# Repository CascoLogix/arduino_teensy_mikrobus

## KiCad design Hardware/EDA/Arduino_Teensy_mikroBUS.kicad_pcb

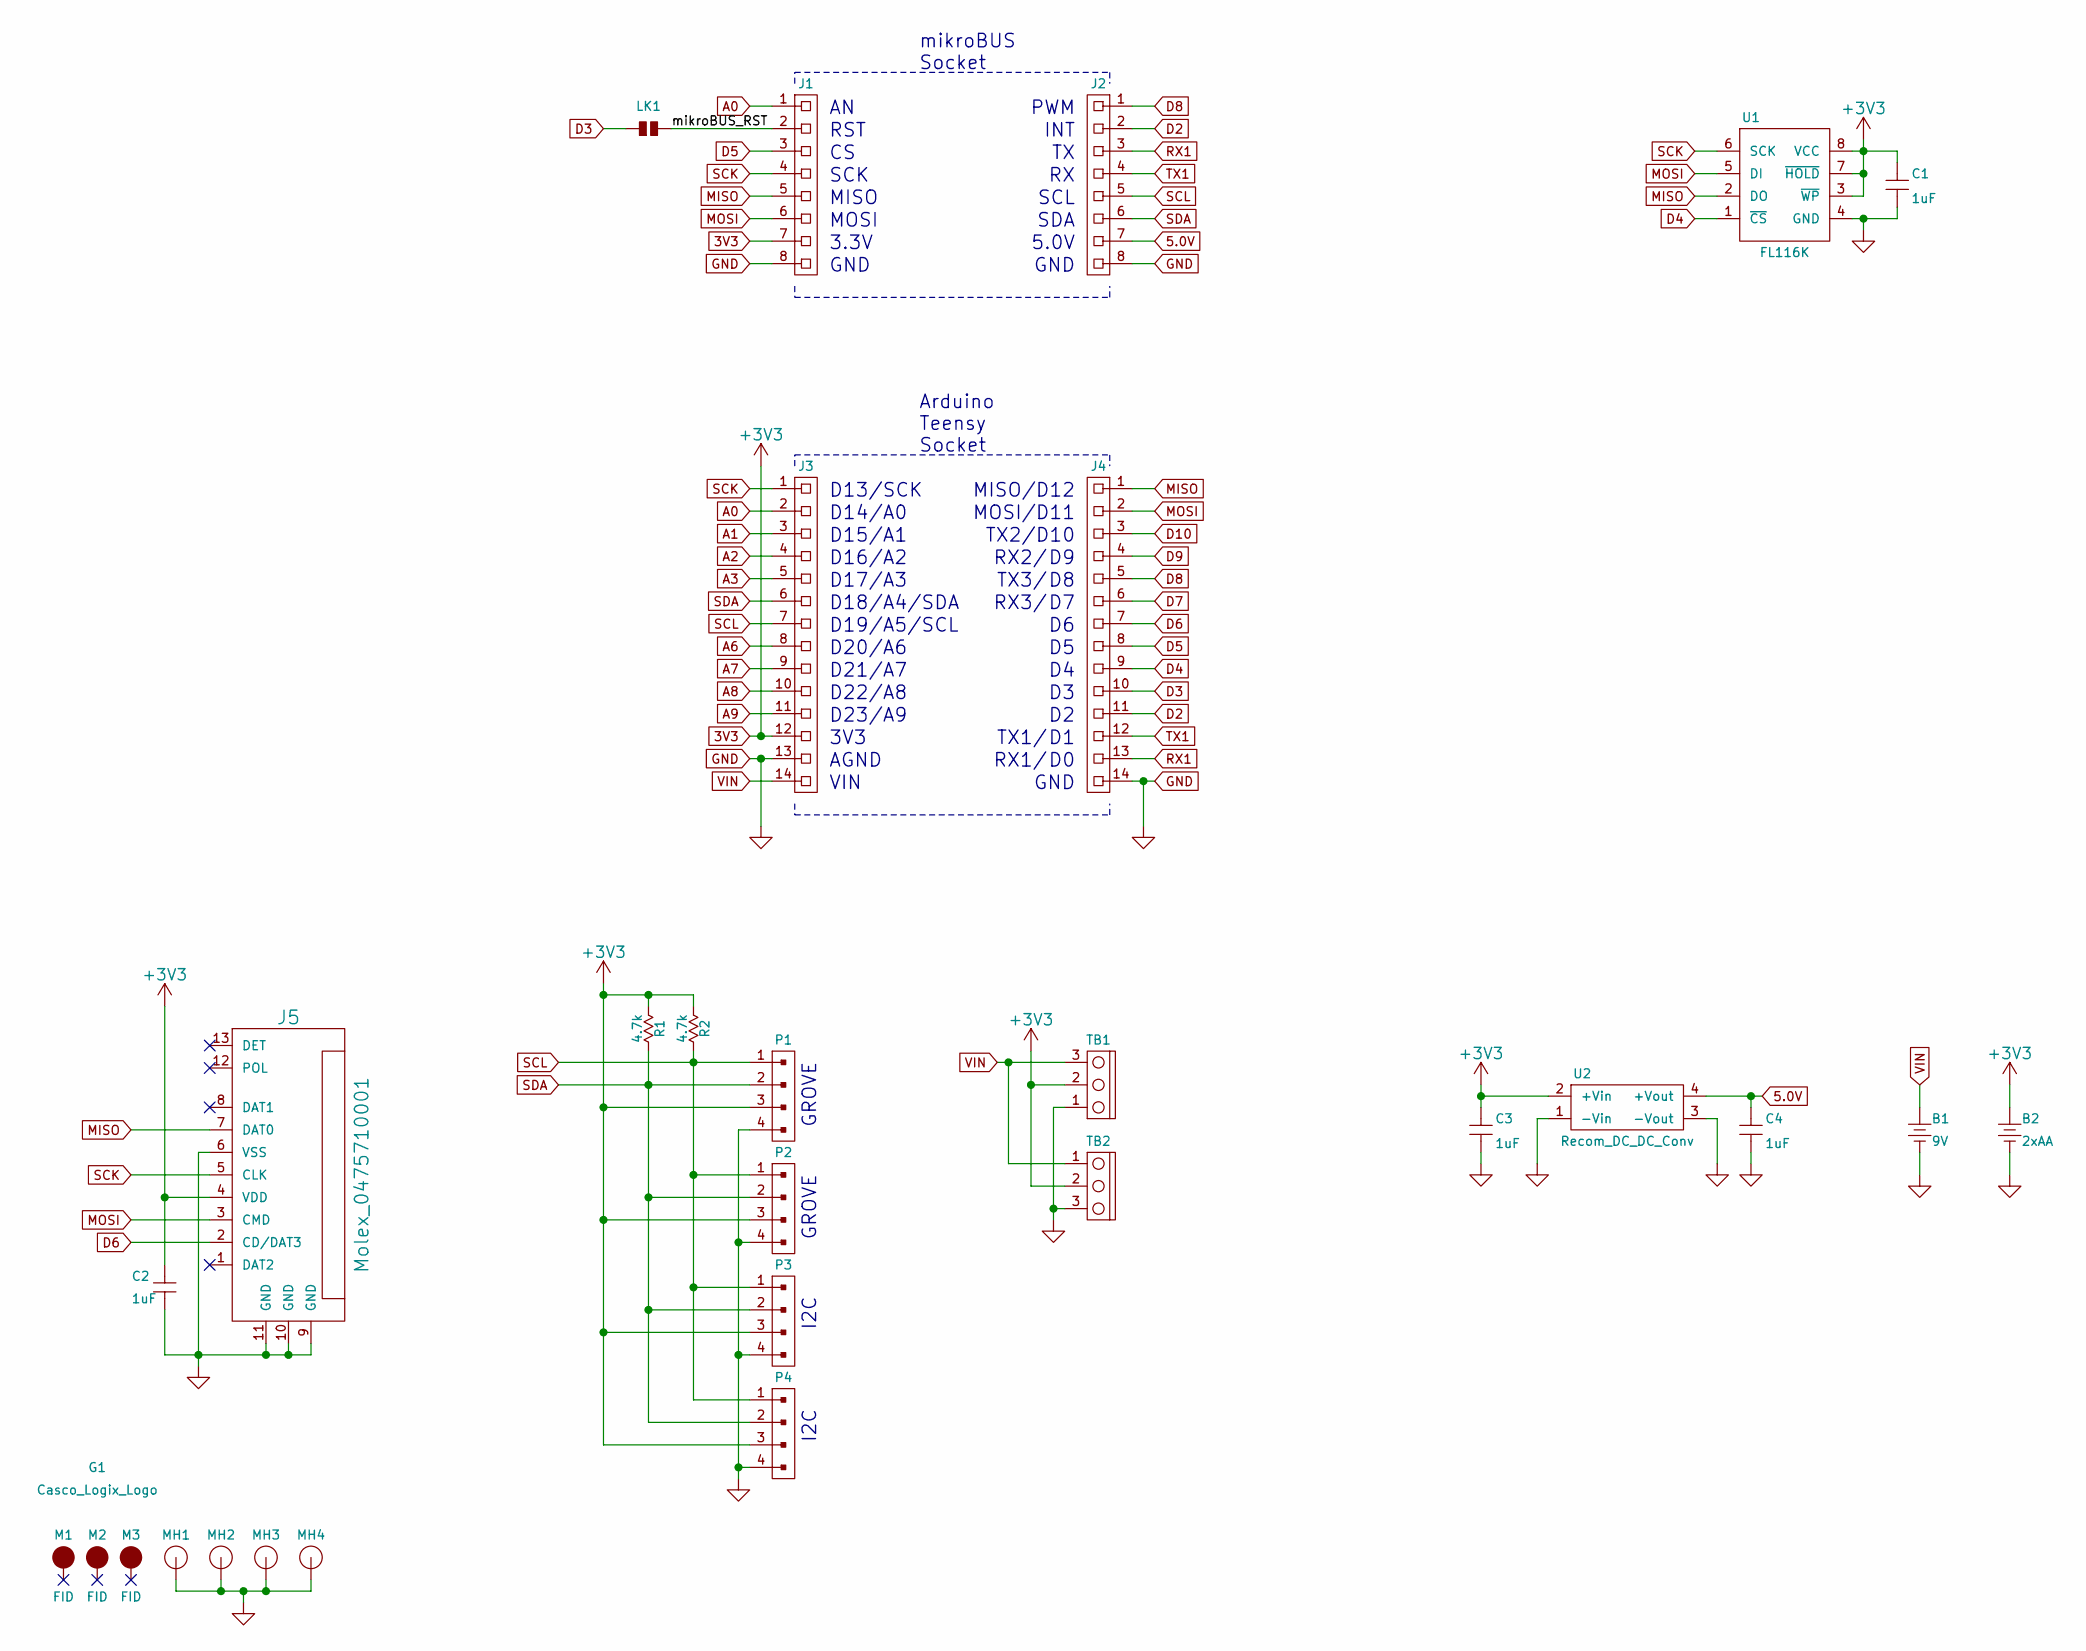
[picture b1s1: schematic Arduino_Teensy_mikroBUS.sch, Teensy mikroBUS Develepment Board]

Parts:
B1: 9V; BC9VPC
B2: 2xAA; Keystone_2462_2AA
C1, C2, C3, C4: 1uF; 0603
G1: Casco_Logix_Logo; Casco_Logix_Logo_7x7MM
J1, J2: HEADER_F_2.54MM_1R8P_ST_AU_PTH
J3, J4: HEADER_F_2.54MM_1R14P_ST_AU_PTH
J5: Molex_0475710001
LK1: SOLDER_LINK_NO
M1, M2, M3: FID; FIDUCIAL
MH1, MH2, MH3, MH4: MTG_HOLE; MH_#6
P1, P2, P3, P4: HEADER_M_2.54MM_1R4P_ST_AU_PTH
R1, R2: 4.7k; R0603
TB1, TB2: OSTVN_1x3; TB_100MIL_1R3P_PTH
U1: FL116K; SO-8
U2: Recom_DC_DC_Conv; Recom_ROE-3.305S

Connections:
3V3: B2.1 (+), C1.1, C2.1, C3.1, J1.7, J3.12, J5.4 (VDD), P1.3, P2.3, P3.3, P4.3, R1.1, R2.1, TB1.2, TB2.2, U1.3 (~WP), U1.7 (~HOLD), U1.8 (VCC), U2.2 (+Vin)
5.0V: C4.1, J2.7, U2.4 (+Vout)
A0: J1.1, J3.2
A1: J3.3
A2: J3.4
A3: J3.5
A6: J3.8
A7: J3.9
A8: J3.10
A9: J3.11
D2: J2.2, J4.11
D3: J4.10, LK1.1
D4: J4.9, U1.1 (~CS)
D5: J1.3, J4.8
D6: J4.7, J5.2 (CD/DAT3)
D7: J4.6
D8: J2.1, J4.5
D9: J4.4
D10: J4.3
GND: B1.2 (-), B2.2 (-), C1.2, C2.2, C3.2, C4.2, J1.8, J2.8, J3.13, J4.14, J5.6 (VSS), J5.9 (GND), J5.10 (GND), J5.11 (GND), MH1.~, MH2.~, MH3.~, MH4.~, P1.4, P2.4, P3.4, P4.4, TB1.1, TB2.3, U1.4 (GND), U2.1 (-Vin), U2.3 (-Vout)
MISO: J1.5, J4.1, J5.7 (DAT0), U1.2 (DO)
MOSI: J1.6, J4.2, J5.3 (CMD), U1.5 (DI)
RX1: J2.3, J4.13
SCK: J1.4, J3.1, J5.5 (CLK), U1.6 (SCK)
SCL: J2.5, J3.7, P1.1, P2.1, P3.1, P4.1, R2.2
SDA: J2.6, J3.6, P1.2, P2.2, P3.2, P4.2, R1.2
TX1: J2.4, J4.12
VIN: B1.1 (+), J3.14, TB1.3, TB2.1
mikroBUS_RST: J1.2, LK1.2

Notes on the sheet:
mikroBUS Socket
Arduino Teensy Socket
RST
SCK
MISO
MOSI
3.3V
GND
PWM
INT
SCL
SDA
5.0V
D10
/A0
3V3
AGND
VIN
/A4/SDA
/A3
GROVE
I2C
MOSI/D11
MISO/D12
D13/SCK
D16
D17
D23
D22
D21
D20
D19
D18
D15
D14
/A2
/A1
/A5/SCL
/A9
/A8

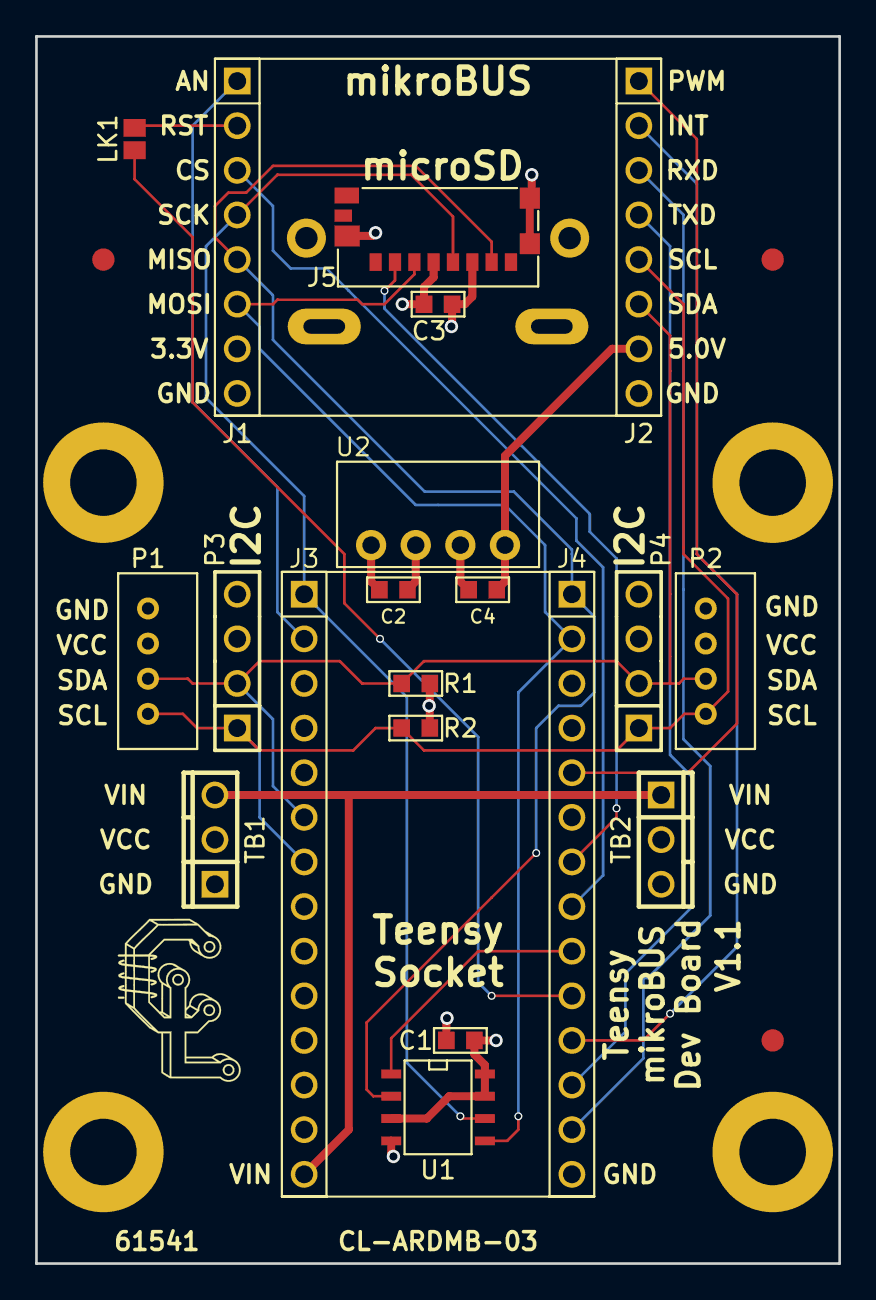
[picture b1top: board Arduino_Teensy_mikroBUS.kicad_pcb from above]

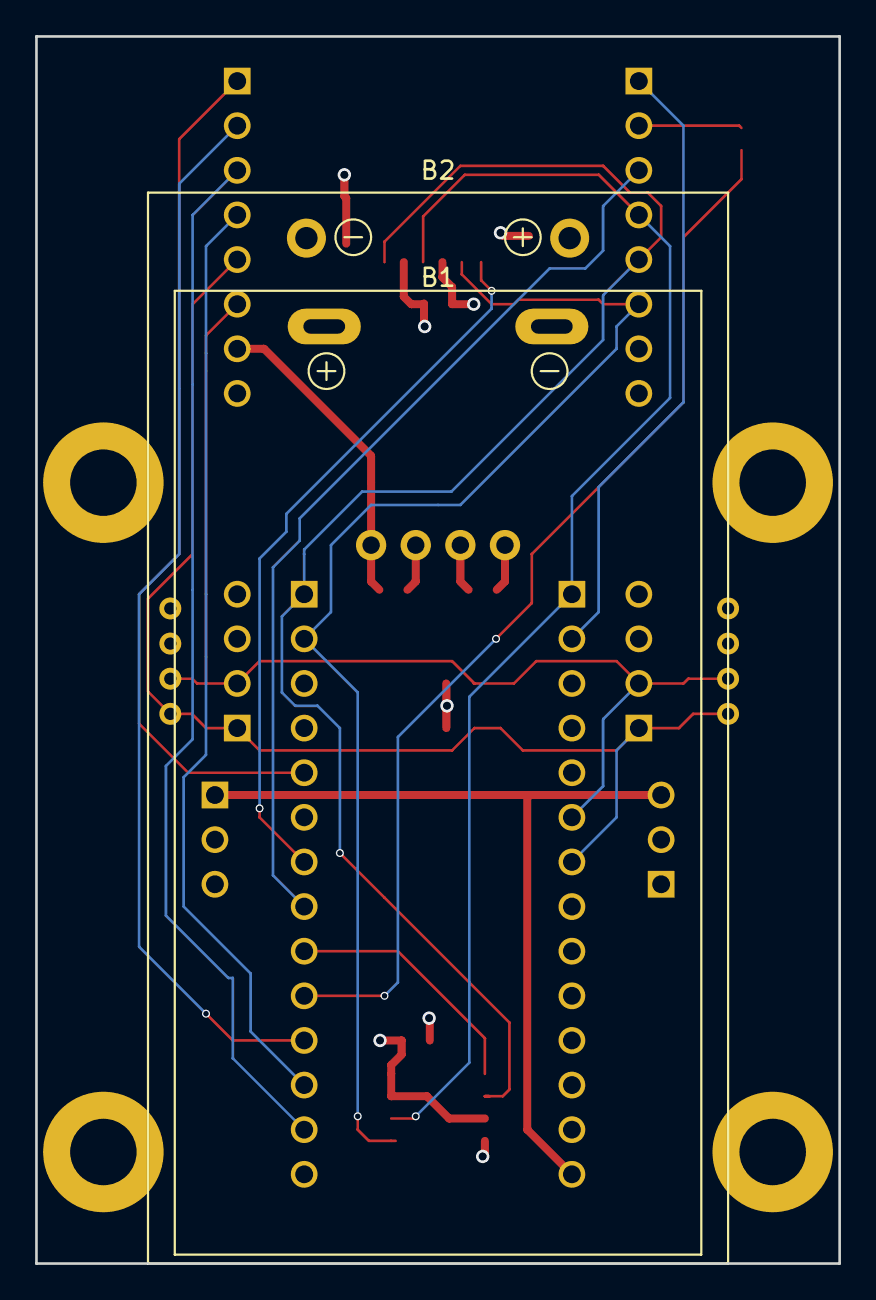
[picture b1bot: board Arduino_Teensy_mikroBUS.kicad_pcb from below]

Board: 4 copper layers, 45.7 x 69.8 mm, 30 parts (2 on the bottom side), 19 nets.

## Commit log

2017-12-28 Initial commit.
2017-12-29 Updated schematic, netlist and read in netlist to PCB file. Added pinouts for Teensy.
2017-12-29 Completed PCB layout, added PCB render image, generated gerbers and schematic.
2018-01-06 Changed PCB outline/size to accomodate mounting holes, but still fit in enclosure. Regenerated Gerbers and PCB render images.
2018-01-14 Adjustment of mounting hole locations was missed. Corrected and updated gerbers and dimensions.
2018-02-17 Added comments to PCB file to indicate updates needed.
2018-02-17 Final changes prior to gerber verification.
2018-04-07 Moved traces near MH2 to clean up layout. Regenerated Gerbers - need to be verified. Updated date in PCB title block. Regenerated PDF schematic.
2018-04-07 Verified gerbers for release.
2018-04-07 Removed change comments from PCB file.
